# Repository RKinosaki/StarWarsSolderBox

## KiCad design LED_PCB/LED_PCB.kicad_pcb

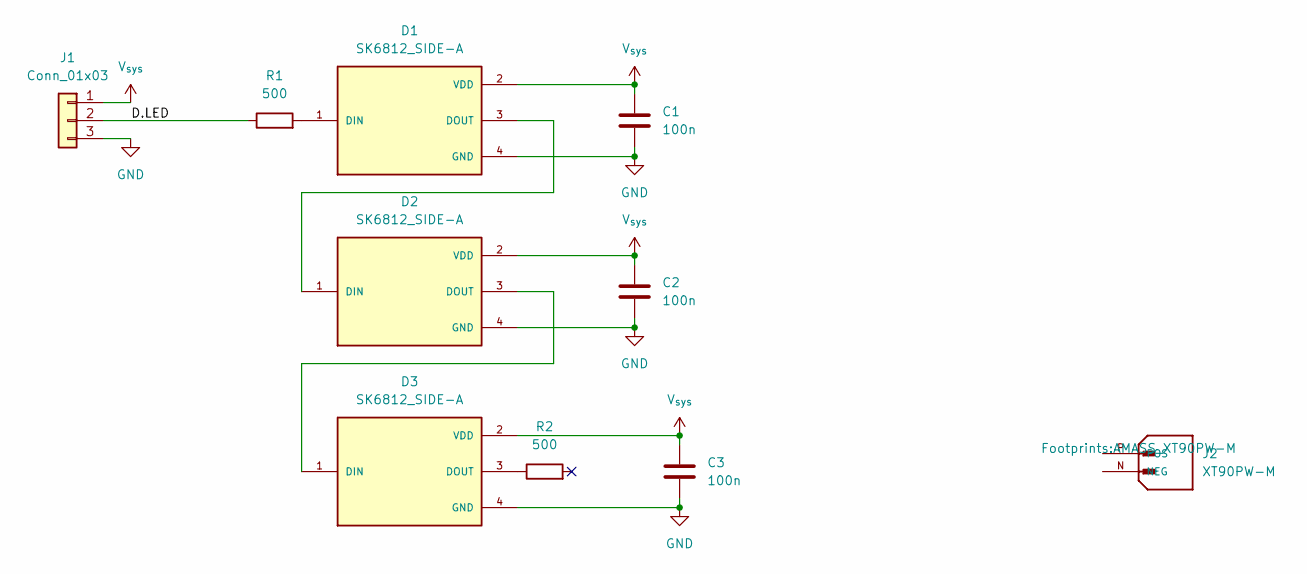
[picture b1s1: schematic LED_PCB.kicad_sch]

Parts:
C1, C2, C3: 100n; C_0402_1005Metric
D1, D2, D3: SK6812_SIDE-A; LED_SK6812_SIDE-A; PARTREV 01
J1: Conn_01x03; JST_PH_S3B-PH-K_1x03_P2.00mm_Horizontal
J2: XT90PW-M; AMASS_XT90PW-M; PARTREV V00
R1, R2: 500; R_0402_1005Metric

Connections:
/D.LED: J1.2, R1.1
GND: C1.2, C2.2, C3.2, D1.4 (GND), D2.4 (GND), D3.4 (GND), J1.3
unnamed: D1.1 (DIN), R1.2
unnamed: D1.3 (DOUT), D2.1 (DIN)
unnamed: D2.3 (DOUT), D3.1 (DIN)
unnamed: D3.3 (DOUT), R2.1
V_{sys}: C1.1, C2.1, C3.1, D1.2 (VDD), D2.2 (VDD), D3.2 (VDD), J1.1

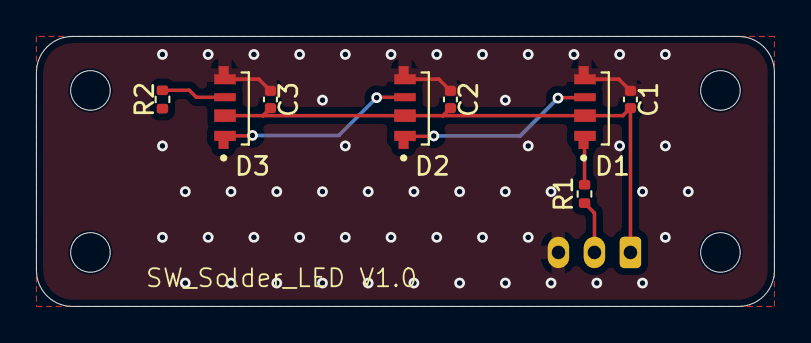
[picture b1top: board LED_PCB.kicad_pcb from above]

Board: 2 copper layers, 41.0 x 15.0 mm, 9 parts (1 on the bottom side), 7 nets.

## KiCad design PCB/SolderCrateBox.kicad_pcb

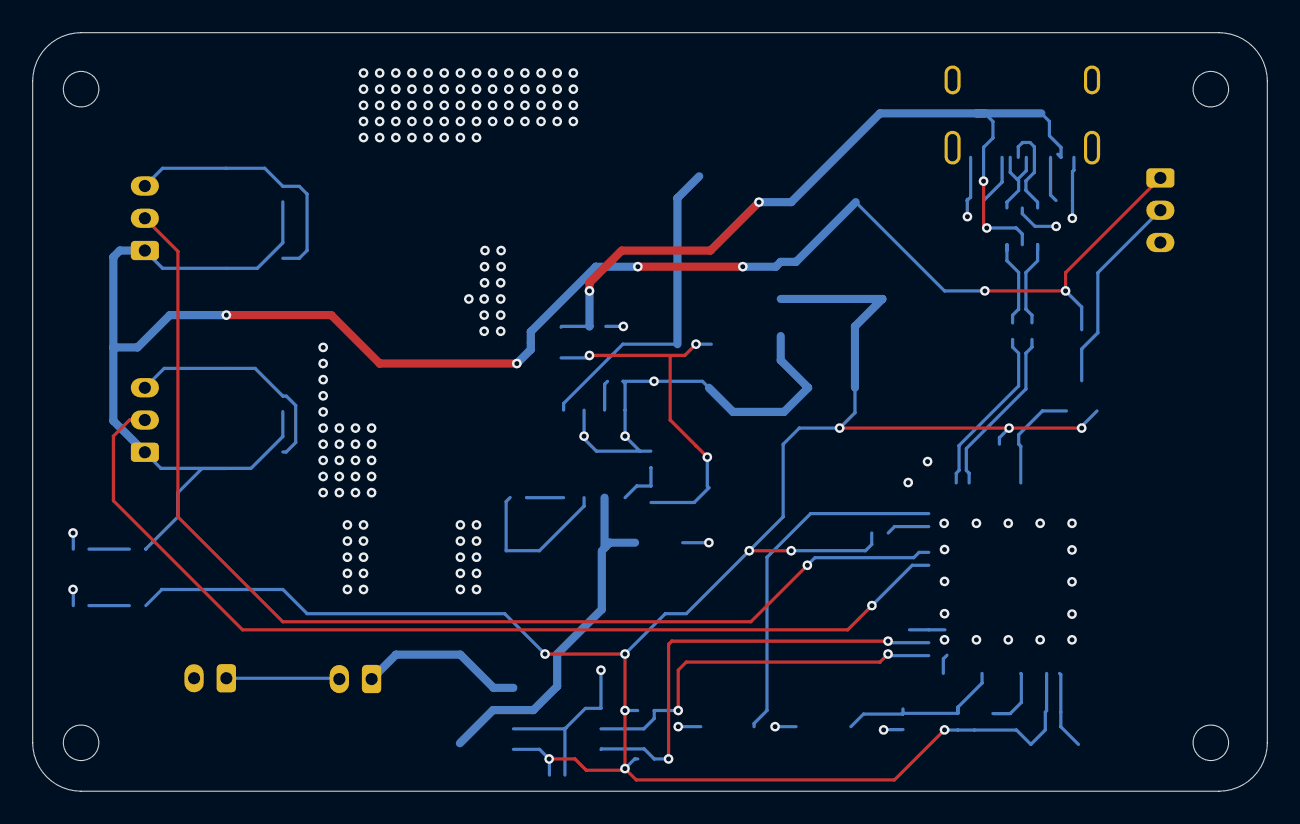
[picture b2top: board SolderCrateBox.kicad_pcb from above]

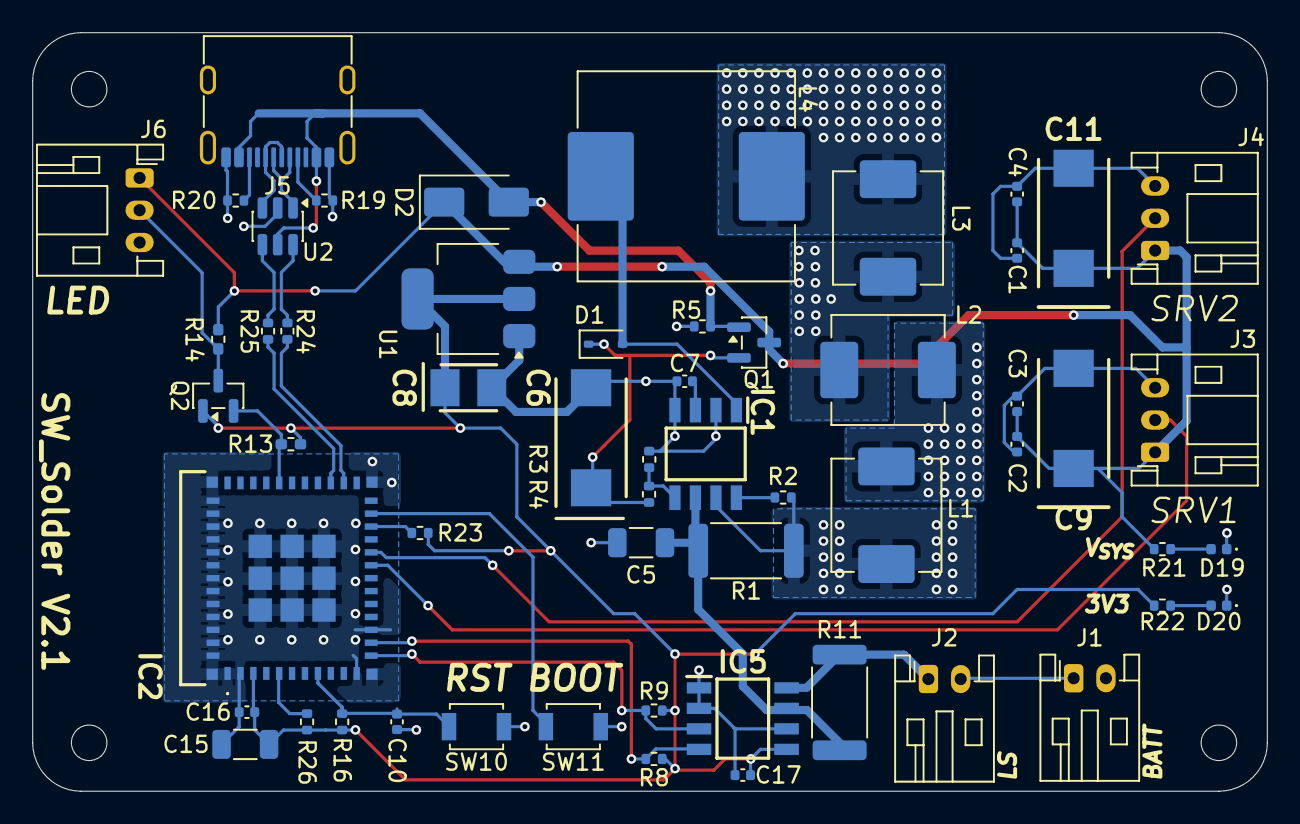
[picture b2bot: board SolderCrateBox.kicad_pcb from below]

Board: 4 copper layers, 76.5 x 47.0 mm, 56 parts (56 on the bottom side), 36 nets.

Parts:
C1, C2, C16, C17: 100n; C_0402_1005Metric
C3, C4: 47u; C_0402_1005Metric
C5: GRM31CR61A107MEA8L; C_1206_3216Metric
C6: TAJD337K010RNJ
C7: 1N5; C_0402_1005Metric
C8: TAJB226K020RNJ
C9, C11: TAJE477K010RNJ
C10: 1u; C_0402_1005Metric
C15: 22u; C_1206_3216Metric
D1: 1N5819WS; D_SOD-323
D2: SS12; D_SMA
D19, D20: LED; LED_0402_1005Metric
IC1: MC34063ADR
IC2: ESP32-C3-MINI-1U-N4X; ESP32C3MINI1UN4X
IC5: INA219AIDR
J1, J2: Conn_01x02; JST_PH_S2B-PH-K_1x02_P2.00mm_Horizontal
J3, J4, J6: Conn_01x03; JST_PH_S3B-PH-K_1x03_P2.00mm_Horizontal
J5: USB_C_Receptacle_USB2.0_16P; USB_C_Receptacle_G-Switch_GT-USB-7010ASV
L1: APH0630T1R0M; L_APV_APH0630
L2: APH0630T220M; L_APV_APH0630
L3: APH0630T470M; L_APV_APH0630
L4: APH1265T101M; L_APV_APH1265
Q1: BSS84; SOT-23
Q2: 2N7002; SOT-23
R1: JER2512F3R220; R_2512_6332Metric
R2: CRCW0402180RJNED; R_0402_1005Metric
R3, R5, R8, R9, R16, R23, R26: 10k; R_0402_1005Metric
R4: 39k; R_0402_1005Metric
R11: 0.01; R_2512_6332Metric
R13, R14: 10k; R_0402_1005Metric_Pad0.72x0.64mm_HandSolder
R19, R20: 5K1; R_0402_1005Metric
R21, R22: 1k; R_0402_1005Metric
R24, R25: 22; R_0402_1005Metric
SW10, SW11: SW_Push; SW_SPST_B3U-1000P
U1: AMS1117-3.3; SOT-223-3_TabPin2
U2: USBLC6-2SC6; SOT-23-6

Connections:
+3V3: C8.1 (+), C15.1, C16.1, C17.1, IC2.3 (3V3), IC5.5 (VS), Q2.1 (G), R8.1, R9.1, R13.1, R16.2, R22.2, R23.1, R26.1, U1.2 (VO)
+V_{BUS}: D2.2 (A), J5.A4 (VBUS), J5.A9 (VBUS), J5.B4 (VBUS), J5.B9 (VBUS), Q1.1 (G), R5.1, U2.5 (VBUS)
+V_{SYS}: C1.1, C2.1, C3.1, C4.1, C9.1 (+), C11.1 (+), D2.1 (K), J3.1, J4.1, J6.1, Q1.3 (D), R14.1, R21.2, U1.3 (VI)
/Boost/BOOST V_{OUT}: C6.1 (+), D1.1 (K), Q1.2 (S), R4.1
/Boost/V_{IN}: C5.1, IC1.6 (VCC), IC5.7 (IN-), R1.1, R11.1
/ESP32_C3/BOOT: IC2.23 (IO9), SW11.1
/ESP32_C3/D+: R25.2, U2.4 (I/O2)
/ESP32_C3/D-: R24.2, U2.6 (I/O1)
/ESP32_C3/DR+: IC2.27 (IO19), R25.1
/ESP32_C3/DR-: IC2.26 (IO18), R24.1
/ESP32_C3/GPIO2: IC2.5 (IO2), R26.2
/ESP32_C3/GPIO8: IC2.22 (IO8), R23.2
/ESP32_C3/RST: C10.1, IC2.8 (EN), R16.1, SW10.1
/ESP32_C3/USB_D+: J5.A6 (D+), J5.B6 (D+), U2.3 (I/O2)
/ESP32_C3/USB_D-: J5.A7 (D-), J5.B7 (D-), U2.1 (I/O1)
/I2C.SCL: IC2.13 (IO1), IC5.4 (SCL), R8.2
/I2C.SDA: IC2.12 (IO0), IC5.3 (SDA), R9.2
/LED.DATA: IC2.31 (TXD0), Q2.2 (S), R13.2
/PWM.SRV1: IC2.19 (IO5), J3.2
/PWM.SRV2: IC2.20 (IO6), J4.2
/VI_Sensor/INA_{IN}: IC5.8 (IN+), J2.1, R11.2
GND: C1.2, C2.2, C3.2, C4.2, C5.2, C6.2 (-), C7.2, C8.2 (-), C9.2 (-), C10.2, C11.2 (-), C15.2, C16.2, C17.2, D19.1 (K), D20.1 (K), IC1.2 (SWITCH_EMITTER), IC1.4 (GND), IC2.1 (GND_1), IC2.2 (GND_2), IC2.11 (GND_3), IC2.14 (GND_4), IC2.36 (GND_5), IC2.37 (GND_6), IC2.38 (GND_7), IC2.39 (GND_8), IC2.40 (GND_9), IC2.41 (GND_10), IC2.42 (GND_11), IC2.43 (GND_12), IC2.44 (GND_13), IC2.45 (GND_14), IC2.46 (GND_15), IC2.47 (GND_16), IC2.48 (GND_17), IC2.49 (GND_18), IC2.50 (GND_19), IC2.51 (GND_20), IC2.52 (GND_21), IC2.53 (GND_22), IC2.54 (GND_23), IC2.55 (GND_24), IC2.56 (GND_25), IC2.57 (GND_26), IC2.58 (GND_27), IC2.59 (GND_28), IC2.60 (GND_29), IC2.61 (GND_30), IC5.1 (A1), IC5.2 (A0), IC5.6 (GND), J1.2, J3.3, J4.3, J5.A1 (GND), J5.A12 (GND), J5.B1 (GND), J5.B12 (GND), J6.3, R3.2, R5.2, R19.2, R20.1, SW10.2, SW11.2, U1.1 (GND), U2.2 (GND)
unnamed: D1.2 (A), IC1.1 (SWITCH_COLLECTOR), L4.1
unnamed: D19.2 (A), R21.1
unnamed: D20.2 (A), R22.1
unnamed: IC1.5 (COMPARATOR_INVERTING_INPUT), R3.1, R4.2
unnamed: IC1.8 (DRIVER_COLLECTOR), R2.1
unnamed: IC1.7 (IPK), L1.2, R1.2, R2.2
unnamed: C7.1, IC1.3 (TIMING_CAPACITOR)
unnamed: J1.1, J2.2
unnamed: J5.A5 (CC1), R19.1
unnamed: J5.B5 (CC2), R20.2
unnamed: J6.2, Q2.3 (D), R14.2
unnamed: L1.1, L2.2
unnamed: L2.1, L3.2
unnamed: L3.1, L4.2

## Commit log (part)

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2026-06-13 Firmware initial commit
2026-06-14 platformio commi
2026-06-14 Completion of servo movement
